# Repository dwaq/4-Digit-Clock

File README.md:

# 4-Digit-Clock
CNC fab-able clock based on the ATMEGA328P

## Hardware
Schematic and Board files created in Autodesk EAGLE 8.

## Software
Software written in Arduino.

Past software was written in C, but had a fatal bug. It was deleted in [commit 8a6b835](https://github.com/dwaq/4-Digit-Clock/commit/8a6b8354e79f4e0a9605a9b12ea75d16f3cf73cc).

## License
This work is licensed under a Creative Commons Attribution 3.0 Unported License.

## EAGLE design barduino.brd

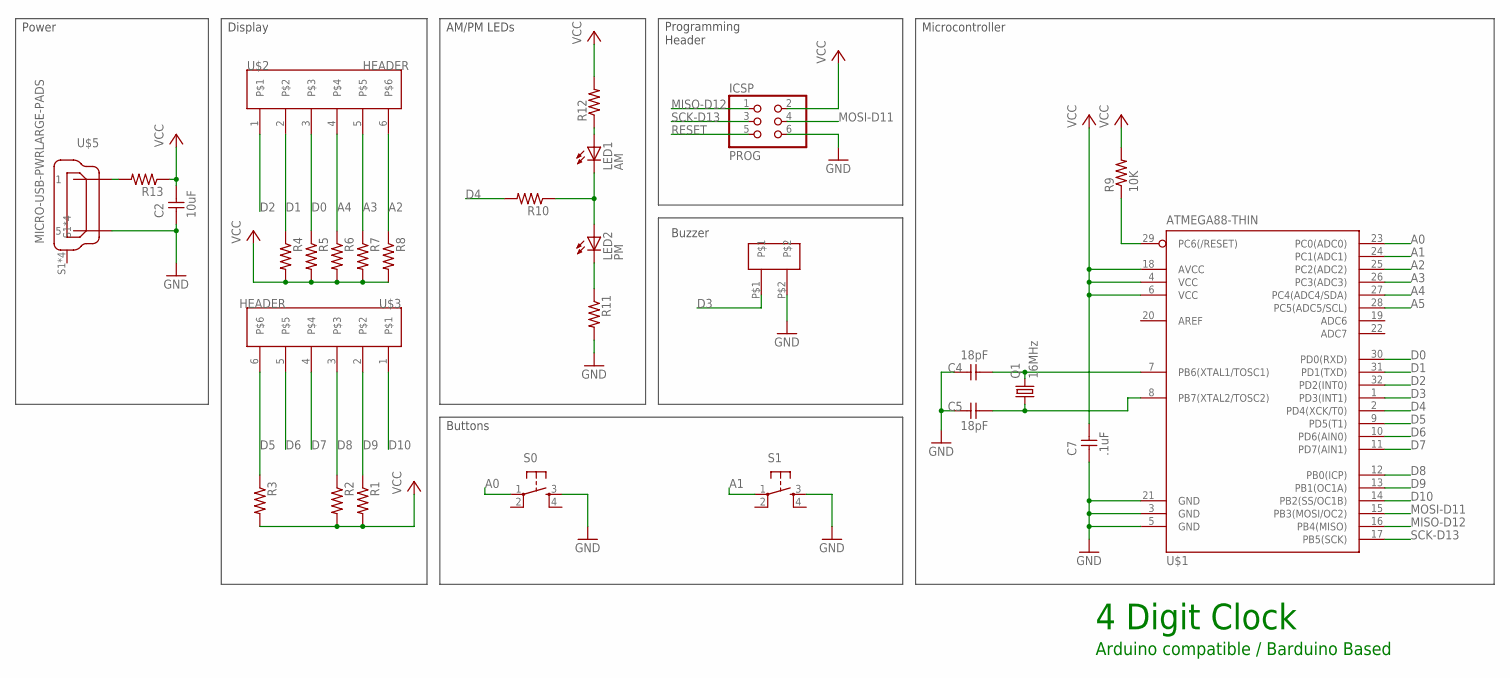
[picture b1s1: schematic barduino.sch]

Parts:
C2: 10uF; 1206
C4, C5: 18pF; 1206
C7: .1uF; 1206
ICSP: PROG; 2X03SMD
LED1: AM; CHIPLED_1206
LED2: PM; CHIPLED_1206
Q1: 16MHz; HC49UP
R1, R2, R3, R4, R5, R6, R7, R8, R10, R11, R12, R13: R-US_R1206; R1206
R9: 10K; 1206
S0, S1: 6MM_SWITCH6MM_SWITCH; 6MM_SWITCH
U$1: ATMEGA88-THIN; TQFP32-08THIN
U$2, U$3: HEADER
U$4: BUZZERLARGE-PADS; CD-1206-SMT-LRG
U$5: MICRO-USB-PWRLARGE-PADS; DX4R005HJ5-PWR-PADS

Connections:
A0: S0.1, U$1.23 (PC0(ADC0))
A1: S1.1, U$1.24 (PC1(ADC1))
A2: R8.1, U$1.25 (PC2(ADC2)), U$2.6
A3: R7.1, U$1.26 (PC3(ADC3)), U$2.5
A4: R6.1, U$1.27 (PC4(ADC4/SDA)), U$2.4
A5: U$1.28 (PC5(ADC5/SCL))
D0: R5.1, U$1.30 (PD0(RXD)), U$2.3
D1: R4.1, U$1.31 (PD1(TXD)), U$2.2
D2: U$1.32 (PD2(INT0)), U$2.1
D3: U$1.1 (PD3(INT1)), U$4.P$1
D4: R10.2, U$1.2 (PD4(XCK/T0))
D5: R3.1, U$1.9 (PD5(T1)), U$3.6
D6: U$1.10 (PD6(AIN0)), U$3.5
D7: U$1.11 (PD7(AIN1)), U$3.4
D8: R2.1, U$1.12 (PB0(ICP)), U$3.3
D9: R1.1, U$1.13 (PB1(OC1A)), U$3.2
D10: U$1.14 (PB2(SS/OC1B)), U$3.1
GND: C2.1, C4.1, C5.1, C7.1, ICSP.6, R11.2, S0.3 (S), S1.3 (S), U$1.3 (GND), U$1.5 (GND), U$1.21 (GND), U$4.P$2, U$5.GND (5)
MISO-D12: ICSP.1, U$1.16 (PB4(MISO))
MOSI-D11: ICSP.4, U$1.15 (PB3(MOSI/OC2))
unnamed: LED1.A, R12.1
unnamed: LED2.C, R11.1
unnamed: LED1.C, LED2.A, R10.1
PB6: C4.2, Q1.2, U$1.7 (PB6(XTAL1/TOSC1))
PB7: C5.2, Q1.1, U$1.8 (PB7(XTAL2/TOSC2))
RESET: ICSP.5, R9.1, U$1.29 (PC6(/RESET))
SCK-D13: ICSP.3, U$1.17 (PB5(SCK))
VCC: C2.2, C7.2, ICSP.2, R1.2, R2.2, R3.2, R4.2, R5.2, R6.2, R7.2, R8.2, R9.2, R12.2, R13.1, R13.2, U$1.4 (VCC), U$1.6 (VCC), U$1.18 (AVCC), U$5.VBUS (1)

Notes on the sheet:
Power
Buttons
Programming Header
4 Digit Clock
Arduino compatible / Barduino Based
Buzzer
Display
AM/PM LEDs
Microcontroller

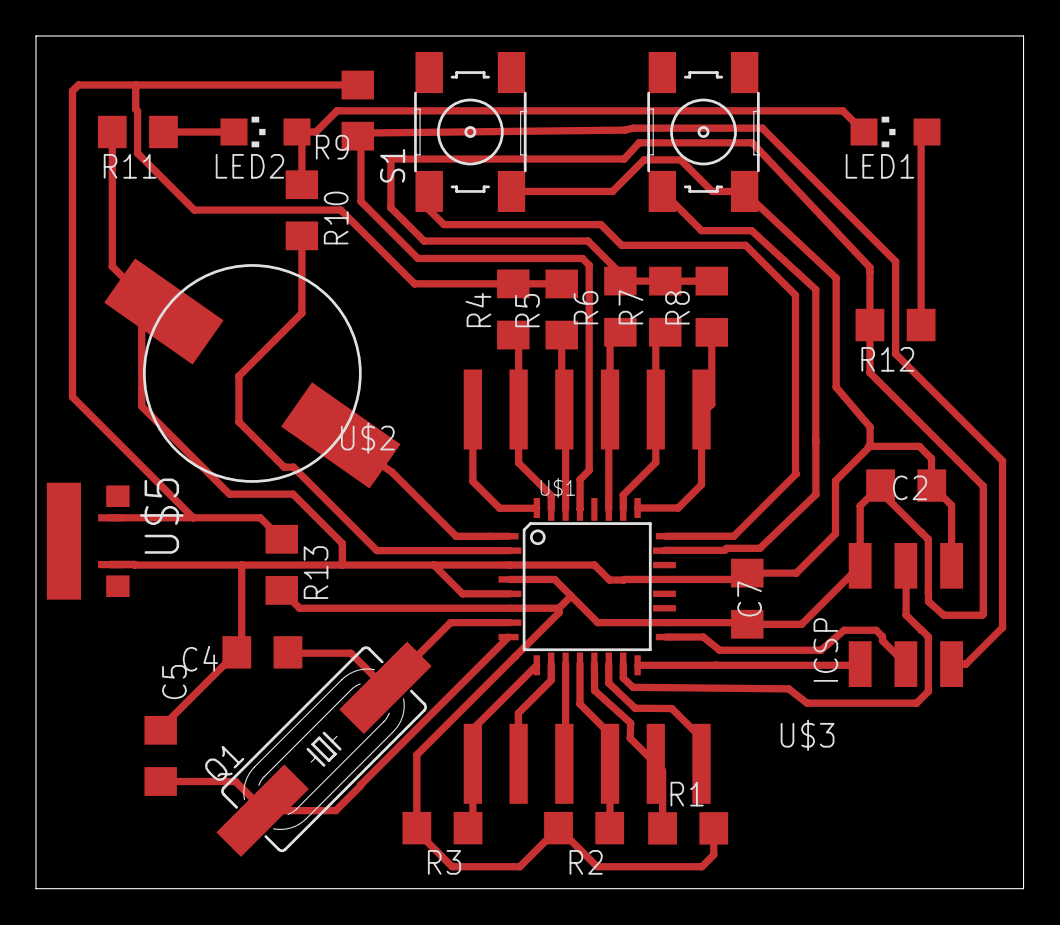
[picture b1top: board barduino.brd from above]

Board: 2 copper layers, 54.9 x 47.4 mm, 28 parts (0 on the bottom side), 27 nets.

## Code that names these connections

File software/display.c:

#include "display.h"
#include "main.h"
#include <wiring_private.h>

// AM/PM LED is on D4 PD4
void ledSetup(void)
{
  DDRD |= (1<<DDD4);
}

// low is AM
void ledAm(void)
{
  PORTD |= (1<<PORTD4);
}

// high is PM
void ledPm(void)
{
  PORTD &= ~(1<<PORTD4);
}

// pinouts for common cathode 7 segment LED display:

// segment is active high
// segment | display | header | mcu
// A  11 D9  PB1
// B  7  D5  PD5
// C  4  D0  PD0
// D  2  A3  PC3
// E  1  A2  PC2
// F  10 D8  PB0
// G  5  D1  PD1
// DP 3  A4  PC4

// digit is active low
// digit | display | header | mcu
// 1  12 D10 PB2
// 2  9  D7  PD7
// 3  8  D6  PD6
// 4  6  D2  PD2

// set display pins to outputs
void displaySetup()
{
  DDRB |= (1<<DDB1 | 1<<DDB0 | 1<<DDB2); // A F 1
  DDRC |= (1<<DDC3 | 1<<DDC2 | 1<<DDC4); // D E DP
  DDRD |= (1<<DDD5 | 1<<DDD0 | 1<<DDD1 | 1<<DDD7 | 1<<DDD6 | 1<<DDD2); // B C G 2 3 4
}

// cycle through and display each digit
// dp is for decimal point: 0 for off; 1 for on
void displayDigits(int dig1, int dig2, int dp, int dig3, int dig4)
{
  setDigit(1, dig1);
  setDigit(2, dig2);
  setDigit(3, dig3);
  setDigit(4, dig4);
  if (dp)
  {
    // display decimal point (special parameter)
    setDigit(2, DP_ON);
  }
  else
  {
    // dont't display decimal point (special parameter)
    setDigit(2, BLANK);
  }

}

// display a number on the selected digit 1, 2, 3, or 4
void setDigit(int digit, int number)
{
  // turn all digits off
  PORTB |= (1<<PORTB2); // 1
  PORTD |= (1<<PORTD7 | 1<<PORTD6 | 1<<PORTD2); // 2 3 4

  // set up segments while digits off,
  // so that the full digit comes up simultanously
  // (although who is going to be able to detect a couple clk cycles?)
  setSegment(number);

  // then turn on specfic digit
  switch(digit)
  {
    case 1:
    // TODO: ONLY when display hours,
    // don't display leading 0
    //if (number != 0)
    //{
        PORTB &= ~(1<<PORTB2); // 1
    //}
      break;
    // this case also handles decimal point
    case 2:
      PORTD &= ~(1<<PORTD7); // 2
      break;
    case 3:
      PORTD &= ~(1<<PORTD6); // 3
      break;
    case 4:
      PORTD &= ~(1<<PORTD2); // 4
      break;
    //default:
      // bad - should't be here
  }
}

// display a number or symbol using the 7 segments
// number can be between 0-9 or settings screen uses A-F
void setSegment(int number)
{
  // first, reset all segments
  PORTB &= ~(1<<PORTB1 | 1<<PORTB0); // A F
  PORTC &= ~(1<<PORTC4 | 1<<PORTC3 | 1<<PORTC2); // DP D E
  PORTD &= ~(1<<PORTD5 | 1<<PORTD0 | 1<<PORTD1); // B C G

  // then set the coorespoding segments
  switch(number)
  {
    case 0:
      // A B C D E F
      PORTB |= (1<<PORTB1 | 1<<PORTB0); // A F
      PORTC |= (1<<PORTC3 | 1<<PORTC2); // D E
      PORTD |= (1<<PORTD5 | 1<<PORTD0); // B C
      break;
    case 1:
      // B C
      PORTD |= (1<<PORTD5 | 1<<PORTD0); // B C
      break;
    case 2:
      // A B D E G
      PORTB |= (1<<PORTB1); // A
      PORTC |= (1<<PORTC3 | 1<<PORTC2); // D E
      PORTD |= (1<<PORTD5 | 1<<PORTD1); // B G
      break;
    case 3:
      // A B C D G
      PORTB |= (1<<PORTB1); // A
      PORTC |= (1<<PORTC3); // D E
      PORTD |= (1<<PORTD5 | 1<<PORTD0 | 1<<PORTD1); // B C G
      break;
    case 4:
      // B C F G
      PORTB |= (1<<PORTB0); // F
      PORTD |= (1<<PORTD5 | 1<<PORTD0 | 1<<PORTD1); // B C G
      break;
    case 5:
      // A C D F G
      PORTB |= (1<<PORTB1 | 1<<PORTB0); // A F
      PORTC |= (1<<PORTC3); // D
      PORTD |= (1<<PORTD0 | 1<<PORTD1); // C G
      break;
    case 6:
      // A C D E F G
      PORTB |= (1<<PORTB1 | 1<<PORTB0); // A F
      PORTC |= (1<<PORTC3 | 1<<PORTC2); // D E
      PORTD |= (1<<PORTD0 | 1<<PORTD1); // C G
      break;
    case 7:
      // A B C
      PORTB |= (1<<PORTB1); // A
      PORTD |= (1<<PORTD5 | 1<<PORTD0); // B C
      break;
    case 8:
      // A B C D E F G
      PORTB |= (1<<PORTB1 | 1<<PORTB0); // A F
      PORTC |= (1<<PORTC3 | 1<<PORTC2); // D E
      PORTD |= (1<<PORTD5 | 1<<PORTD0 | 1<<PORTD1); // B C G
      break;
    case 9:
      // A B C D F G
      PORTB |= (1<<PORTB1 | 1<<PORTB0); // A F
      PORTC |= (1<<PORTC3); // D
      PORTD |= (1<<PORTD5 | 1<<PORTD0 | 1<<PORTD1); // B C G
      break;
    case 0xA:
      // A B C E F G
      PORTB |= (1<<PORTB1 | 1<<PORTB0); // A F
      PORTC |= (1<<PORTC2); // E
      PORTD |= (1<<PORTD5 | 1<<PORTD0 | 1<<PORTD1); // B C G
      break;
    case 0xB:
      // A B C D E F G
      PORTB |= (1<<PORTB1 | 1<<PORTB0); // A F
      PORTC |= (1<<PORTC3 | 1<<PORTC2); // D E
      PORTD |= (1<<PORTD5 | 1<<PORTD0 | 1<<PORTD1); // B C G
      break;
    case 0xC:
      // A D E F
      PORTB |= (1<<PORTB1 | 1<<PORTB0); // A F
      PORTC |= (1<<PORTC3 | 1<<PORTC2); // D E
      break;
    case 0xD:
      // A B C D E F
      PORTB |= (1<<PORTB1 | 1<<PORTB0); // A F
      PORTC |= (1<<PORTC3 | 1<<PORTC2); // D E
      PORTD |= (1<<PORTD5 | 1<<PORTD0); // B C
      break;
    case 0xE:
      // A D E F G
      PORTB |= (1<<PORTB1 | 1<<PORTB0); // A F
      PORTC |= (1<<PORTC3 | 1<<PORTC2); // D E
      PORTD |= (1<<PORTD1); // G
      break;
    case 0xF:
      // A E F G
      PORTB |= (1<<PORTB1 | 1<<PORTB0); // A F
      PORTC |= (1<<PORTC2); // E
      PORTD |= (1<<PORTD1); // G
      break;
    case N:
      // A B C E F
      PORTB |= (1<<PORTB1 | 1<<PORTB0); // A F
      PORTC |= (1<<PORTC2); // E
      PORTD |= (1<<PORTD5 | 1<<PORTD0); // B C
      break;
    case DP_ON:
      // DP
      PORTC |= (1<<PORTC4);
      break;
    //default:
      // case BLANK falls through here
      // just turns off the segment by initial "reset all segments" code
  }
}

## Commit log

2017-05-31 Based on barduino
    http://fabacademy.org/archives/content/projects/barduino/index.html
2017-05-31 Add Eagle project file
2017-05-31 convert to new eagle format
2017-05-31 add microbuilder library
    has through hole 4 digit display
2017-05-31 Stripped a lot and added some clock parts
2017-05-31 Replace pwr jack with usb conn
2017-05-31 clean up a little
2017-05-31 remove reest button
2017-05-31 clean up
2017-05-31 moving things
2017-06-01 replace clock part with 2 custom headers
2017-06-01 display and buttons connected
2017-06-01 lots of routing
2017-06-01 some changes before moving the USB conn
2017-06-01 USB move is going well
2017-06-01 board fully laid out
2017-06-01 remove crossover resistor
2017-06-01 remove VCC resistor
2017-06-01 create buzzer surface mount footprint
2017-06-01 put new buzzer on board
2017-06-01 move buttons to top
2017-06-01 bring in board outline
2017-06-01 mirror header to match pcb layout
2017-06-01 add current limiting resistors to the 4 digits
2017-06-01 connect some missing wires
2017-06-01 closed eagle
2017-08-02 generated gerbers
2017-08-02 need definitions to set pins
2017-08-02 define display pinout
2017-08-02 starter code
    from http://www.crash-bang.com/getting-started-atmel-studio/
2017-08-02 remove test function
2017-08-02 define possible functions
2017-08-02 reset pullup resistor should be 10k
2017-08-02 inverted logic
2017-08-02 add enough display code to get it to compile
2017-08-02 update main to display all segments
2017-08-02 add Makefile generated from MFile
2017-08-02 add switch statement to segment
2017-08-02 starter code to reset and set all segments
2017-08-02 set display pins to outputs
2017-08-02 ignore compiled files
2017-08-02 remove default case since it's not used
2017-08-02 should write segments correctly
2017-08-02 display all digits in loop
2017-08-02 code to turn on each digit
2017-08-02 add digits that need displayed
2017-08-02 remove files from avr-studio
2017-08-02 typo on pin for G segment
2017-08-02 forgot to change digit 2 to digit 3 segments
2017-08-02 write code to control decimal point
2017-08-02 count up from 0-9 and flash decimal point
2017-08-02 add thoughts about future changes
2017-08-13 another file from avr-studio
2017-08-13 new timer method for accurate 1sec
2017-08-13 moving dp update to end helps with dimness
2017-08-13 proper function prototype
2017-08-13 idea to update like a clock
    not working...?
2017-08-15 had digit logic inverted
2017-08-15 set decimal point correctly
2017-08-15 bring back display code and also handle hours
2017-08-15 don't display leading 0 on hours
2017-08-15 after 12 o'clock, its 1 o'clock
2017-08-15 reminder for later
2017-08-16 move 1 sec timer init into new function
2017-08-16 fix comments
2017-08-16 new variable that toggles between HH:MM and MM:SS
2017-08-16 rename to keep same naming
2017-08-16 add button setup code
2017-08-16 add pin change interrupt handler
2017-08-16 add settings typedef
2017-08-16 only change display in DISPLAY mode
2017-08-16 fix some warnings
2017-08-16 move between settings state with S1
2017-08-17 fix comment
2017-08-17 indent correctly
2017-08-17 use define for turning decimal point on
2017-08-17 display hex digits
2017-08-17 move decimal point code to the end
2017-08-17 fix and generalize comments
2017-08-17 start to implement settings view
2017-08-17 rename variable to generalize it
2017-08-17 set values to typedef to simplify display logic
2017-08-17 code to display letter n for "on"
2017-08-17 flesh out settings display
2017-08-17 top counting time when you're trying to set it
2017-08-17 handle S2 button presses in settings
2017-08-17 add new 1206 AM and PM LEDs
2017-08-17 add border around schematic and values
2017-08-17 eagle switched names of temp files
2017-08-17 add am/pm led code
2017-08-17 put increase hour code into function
2017-10-08 ignore lock file
2017-10-08 combine all code into 1 file
2017-10-08 don't need while in loop
2017-10-08 use TimerOne library instead of timer registers
2017-10-08 use Arduino-style button interrupts
2017-10-08 disable/restart timer when setting time
2017-10-08 move from test code to actual clock counting
2017-10-08 work around special cases for displaying leading 0
2017-10-08 messed up displaying E and F
2017-10-08 add deboucing to buttons
2017-10-08 play tone on button press
2017-10-08 rename variable to make it clear what it is
2017-10-08 play hourly chime if enabled
2017-10-12 Add resistors to segments, not digits
    1. Renamed reset and AM/PM LED R's
    2. Fixed error on LED net
    3. Moved/added resistors to all 8 segments
    4. Updated eagle
2017-10-12 attached resistors
    need to fix buttons and reset
2017-10-12 ugly but everything connected
2017-10-12 made the routing pretty(ier)
2017-10-12 make a new mini USB connector that doesn't have data lines since they're not used
2017-10-12 Put new USB power connector on sch/brd
2017-10-12 Buttons don't have a value
2017-10-12 updated eagle; closed project
2017-10-16 replace thru hole (mistake) with surface mount USB connector
2017-10-16 remove thru hole part from library
2017-10-16 ignore temp library files
2017-10-16 Explain that TimerOne library needs installed
2017-10-17 update sch to correctly light AM/PM LEDs
2017-10-17 start new AM/PM LED layout
2017-10-17 align schematic, add another resistor
2017-10-17 fixed mistake on LEDs net
2017-10-18 add alarm struct
2017-10-18 add AM/PM to alarm hr
2017-10-18 add time struct and replace min_10 and min_1 with only min
2017-10-18 change variable name so it doesn't interfer with arduino library
2017-10-18 use const instead of define for settings states
2017-10-18 remind myself about alarm am/pm led
2017-10-18 fix comments on counting seconds code
2017-10-18 move dp and display into clock struct
2017-10-18 move display code into its own file and make a main header
2017-10-18 rename and move Arduino software files
2017-10-18 Update README with HW and SW info
2017-10-18 Add license
2017-10-20 only chime in clock mode (not while setting time)
2017-10-20 increase tone length on the hour
2017-10-20 move button tone into new function
2017-10-20 handle button presses in main loop instead of interrupts
2017-10-20 move hour function to the bottom of the code
2017-10-20 time starts at 12 pm
2017-10-20 time moves from AM to PM at 12, not 13
2017-10-20 alarm time also moves from AM to PM at 12, not 13
2017-10-20 in alarm hr setting, use LED to display time of day
2017-10-20 and remember to set it back to the regular time of day afterwards
2017-10-20 don't display leading 0 for hours
2017-10-20 add checking for if alarm should go off
2017-10-20 pressing any button stops alarm
2017-10-20 alarm off by default
2018-01-15 duplicate micro USB symbol from mini USB
2018-01-15 add shield connection
2018-01-15 replace mini usb connector with micro usb
2018-01-15 add pads with dimensions and placement
2018-01-15 create and connect device
2018-01-15 add pin names, outline, text
2018-01-15 replace crystal with new footprint part
2018-01-15 connect usb micro connector with jumper
    also reduces the board size
2018-01-15 remove small traces inside microcontroller
2018-01-15 use specific footprint for buzzer
2018-01-15 only a couple air wires left
2018-01-15 connected most signals
    still some air wires left
2018-01-15 move crystal into place
2018-01-15 go back to original board size
2018-01-15 rip up some wires
2018-01-15 connected RESET
2018-01-15 finally fixed that buzzer connection
2018-01-15 ignore airwire on jumper
2018-01-15 removed temp file
2018-01-16 Reroute some signals so it can actually be built
2018-01-16 fix ERC errors
2018-01-16 fix air wires
2018-02-07 add an image of the layout, ok
2018-02-07 add image of schematic, ok
2018-02-11 alarm code was in the wrong section
2018-02-11 add comment about alarm
2018-02-11 add pull ups on display resistors
2018-02-11 new buzzer footprint with larger pads
2018-02-11 new USB footprint with single, large pad
2018-02-12 only add Brandon's layout changes
2018-02-12 fix unconnected segments
2018-02-14 connect new buzzer variant
2018-02-14 connect new usb variant
2018-02-14 change to new USB and buzzer footprint on schematic and layout
